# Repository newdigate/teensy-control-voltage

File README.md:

# teensy control voltage analog computer shield 

[![built with kicad](https://img.shields.io/badge/project-v5.1.6-brightgreen.svg?label=kicad&colorA=555555&colorB=8a8fff&logo=
)](https://kicad.org/)

**open source [hardware](hardware) ~~and [software](software)~~ for a [teensy 4.1](https://www.pjrc.com/store/teensy40.html "teensy 4.1 board") eurorack control voltage shield** 

extend a [teensy 4.1](https://www.pjrc.com/store/teensy40.html "teensy 4.1 board") with peripherals to interface with eurorack modular equipment. 

## specifications
* **microcontrollers:** 
  * 600 Mhz ARM cortex m7 ( [teensy 4.1 board](https://www.pjrc.com/store/teensy41.html "teensy 4.1 board") )
* **display:** ST7735 128x128 16bit-color tft display
* **breakouts:** 
  * microSD card socket, 
  * USB host/device, 
  * midi in/out, 
  * 1 x encoders w/switch
* **panel:** 14HP aluminium panel mounted for eurorack case
* **programability**: 
  * write arduino compatible c/c++ firmware & program using arduino/teensyduino
  * arm gnu toolchain [downloads](https://developer.arm.com/tools-and-software/open-source-software/developer-tools/gnu-toolchain/gnu-rm/downloads)
  * teensy [audio library](https://www.pjrc.com/teensy/gui/)

## MIT open source license
* MIT license unless otherwise specified on a per file basis.

## Open source software stack
* All [schematics](hardware/CIRCUITS.md) and boards are created using [Kicad](http://kicad.org/) 
* All mechanical designs are created using [FreeCAD](https://github.com/FreeCAD/FreeCAD)
* Some images have been rendered using [Blender 2.81](https://www.blender.org/)

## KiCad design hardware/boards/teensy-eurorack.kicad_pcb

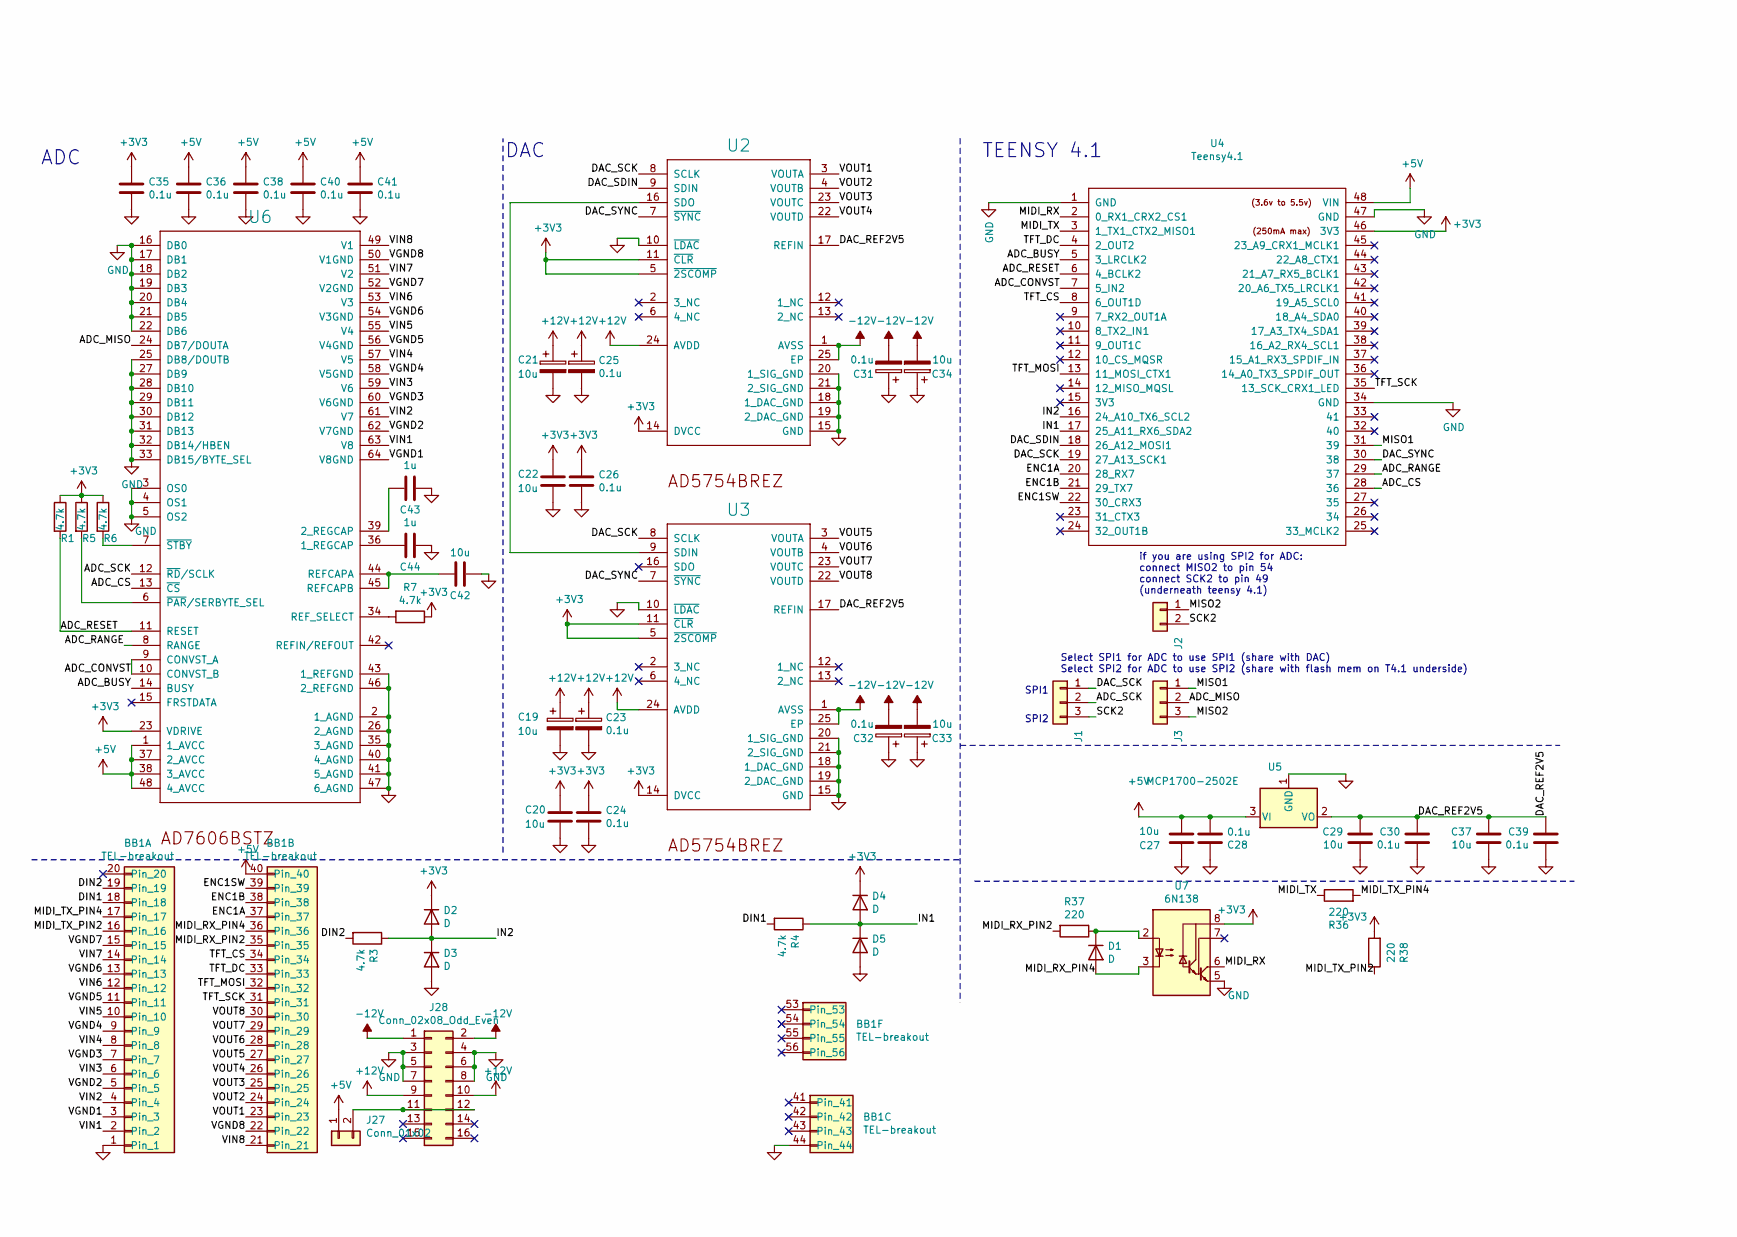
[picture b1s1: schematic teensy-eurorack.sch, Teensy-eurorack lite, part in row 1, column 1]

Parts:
BB1: TEL-breakout; TElite-breakout-board
C19, C21, C33, C34: 10u; CP_Radial_D5.0mm_P2.00mm
C20, C22, C27, C29, C37, C42: 10u; C_0805_2012Metric
C23, C25, C31, C32: 0.1u; CP_Radial_D5.0mm_P2.00mm
C24, C26, C28, C30, C35, C36, C38, C39, C40, C41: 0.1u; C_0805_2012Metric
C43, C44: 1u; C_0805_2012Metric
D1, D2, D3, D4, D5: D; D_0805_2012Metric
J1, J3: Conn_01x03; Pin_Header_Straight_1x03_Pitch2.54mm
J2: Conn_01x02; Pin_Header_Straight_1x02_Pitch2.54mm
J27: Conn_01x02; PinHeader_1x02_P2.54mm_Vertical
J28: Conn_02x08_Odd_Even; PinHeader_2x08_P2.54mm_Vertical
R1, R3, R4, R5, R6, R7: 4.7k; R_0805_2012Metric
R36, R37, R38: 220; R_0805_2012Metric
U2, U3: AD5754BREZ; HTSSOP-24-1EP_4.4x7.8mm_P0.65mm_EP3.2x5mm
U4: Teensy4.1; Teensy41_tht
U5: MCP1700-2502E; SOT-23
U6: AD7606BSTZ; LQFP-64_10x10mm_P0.5mm
U7: 6N138; 6N138S

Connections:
+3V3: C20.1, C22.1, C24.1, C26.1, C35.1, D2.1 (K), D4.1 (K), R1.1, R5.1, R6.1, R7.1, R38.2, U2.5 (~2SCOMP~), U2.11 (~CLR~), U2.14 (DVCC), U3.5 (~2SCOMP~), U3.11 (~CLR~), U3.14 (DVCC), U4.46 (3V3), U6.23 (VDRIVE), U7.8 (VCC)
+5V: BB1.40, C27.2, C28.2, C36.1, C38.1, C40.1, C41.1, J27.1, U4.48 (VIN), U5.3 (VI), U6.1 (1_AVCC), U6.37 (2_AVCC), U6.38 (3_AVCC), U6.48 (4_AVCC)
+12V: C19.1, C21.1, C23.1, C25.1, J28.9, J28.10, U2.24 (AVDD), U3.24 (AVDD)
-12V: C31.2, C32.2, C33.2, C34.2, J28.1, J28.2, U2.1 (AVSS), U2.25 (EP), U3.1 (AVSS), U3.25 (EP)
/ADC_BUSY: U4.5 (3_LRCLK2), U6.14 (BUSY)
/ADC_CONVST: U4.7 (5_IN2), U6.9 (CONVST_A), U6.10 (CONVST_B)
/ADC_CS: U4.28 (36), U6.13 (~CS~)
/ADC_MISO: J3.2, U6.24 (DB7/DOUTA)
/ADC_RANGE: U4.29 (37), U6.8 (RANGE)
/ADC_RESET: R1.2, U4.6 (4_BCLK2), U6.11 (RESET)
/ADC_SCK: J1.2, U6.12 (~RD~/SCLK)
/DAC_REF2V5: C29.1, C30.1, C37.1, C39.1, U2.17 (REFIN), U3.17 (REFIN), U5.2 (VO)
/DAC_SCK: J1.1, U2.8 (SCLK), U3.8 (SCLK), U4.19 (27_A13_SCK1)
/DAC_SDIN: U2.9 (SDIN), U4.18 (26_A12_MOSI1)
/DAC_SYNC: U2.7 (~SYNC~), U3.7 (~SYNC~), U4.30 (38)
/DIN1: BB1.18, R4.2
/DIN2: BB1.19, R3.2
/ENC1A: BB1.37, U4.20 (28_RX7)
/ENC1B: BB1.38, U4.21 (29_TX7)
/ENC1SW: BB1.39, U4.22 (30_CRX3)
/IN1: D4.2 (A), D5.1 (K), R4.1, U4.17 (25_A11_RX6_SDA2)
/IN2: D2.2 (A), D3.1 (K), R3.1, U4.16 (24_A10_TX6_SCL2)
/MIDI_RX: U4.2 (0_RX1_CRX2_CS1), U7.6 (VO2)
/MIDI_RX_PIN2: BB1.35, R37.2
/MIDI_RX_PIN4: BB1.36, D1.2 (A), U7.3 (C2)
/MIDI_TX: R36.1, U4.3 (1_TX1_CTX2_MISO1)
/MIDI_TX_PIN2: BB1.16, R38.1
/MIDI_TX_PIN4: BB1.17, R36.2
/MISO1: J3.1, U4.31 (39)
/MISO2: J2.1, J3.3
/SCK2: J1.3, J2.2
/TFT_CS: BB1.34, U4.8 (6_OUT1D)
/TFT_DC: BB1.33, U4.4 (2_OUT2)
/TFT_MOSI: BB1.32, U4.13 (11_MOSI_CTX1)
/TFT_SCK: BB1.31, U4.35 (13_SCK_CRX1_LED)
/VGND1: BB1.3, U6.64 (V8GND)
/VGND2: BB1.5, U6.62 (V7GND)
/VGND3: BB1.7, U6.60 (V6GND)
/VGND4: BB1.9, U6.58 (V5GND)
/VGND5: BB1.11, U6.56 (V4GND)
/VGND6: BB1.13, U6.54 (V3GND)
/VGND7: BB1.15, U6.52 (V2GND)
/VGND8: BB1.22, U6.50 (V1GND)
/VIN1: BB1.2, U6.63 (V8)
/VIN2: BB1.4, U6.61 (V7)
/VIN3: BB1.6, U6.59 (V6)
/VIN4: BB1.8, U6.57 (V5)
/VIN5: BB1.10, U6.55 (V4)
/VIN6: BB1.12, U6.53 (V3)
/VIN7: BB1.14, U6.51 (V2)
/VIN8: BB1.21, U6.49 (V1)
/VOUT1: BB1.23, U2.3 (VOUTA)
/VOUT2: BB1.24, U2.4 (VOUTB)
/VOUT3: BB1.25, U2.23 (VOUTC)
/VOUT4: BB1.26, U2.22 (VOUTD)
/VOUT5: BB1.27, U3.3 (VOUTA)
/VOUT6: BB1.28, U3.4 (VOUTB)
/VOUT7: BB1.29, U3.23 (VOUTC)
/VOUT8: BB1.30, U3.22 (VOUTD)
GND: BB1.1, BB1.44, C19.2, C20.2, C21.2, C22.2, C23.2, C24.2, C25.2, C26.2, C27.1, C28.1, C29.2, C30.2, C31.1, C32.1, C33.1, C34.1, C35.2, C36.2, C37.2, C38.2, C39.2, C40.2, C41.2, C42.1, C43.1, C44.1, D3.2 (A), D5.2 (A), J28.3, J28.4, J28.5, J28.6, J28.7, J28.8, U2.10 (~LDAC~), U2.15 (GND), U2.18 (1_DAC_GND), U2.19 (2_DAC_GND), U2.20 (1_SIG_GND), U2.21 (2_SIG_GND), U3.10 (~LDAC~), U3.15 (GND), U3.18 (1_DAC_GND), U3.19 (2_DAC_GND), U3.20 (1_SIG_GND), U3.21 (2_SIG_GND), U4.1 (GND), U4.34 (GND), U4.47 (GND), U5.1 (GND), U6.2 (1_AGND), U6.3 (OS0), U6.4 (OS1), U6.5 (OS2), U6.16 (DB0), U6.17 (DB1), U6.18 (DB2), U6.19 (DB3), U6.20 (DB4), U6.21 (DB5), U6.22 (DB6), U6.25 (DB8/DOUTB), U6.26 (2_AGND), U6.27 (DB9), U6.28 (DB10), U6.29 (DB11), U6.30 (DB12), U6.31 (DB13), U6.32 (DB14/HBEN), U6.33 (DB15/BYTE_SEL), U6.35 (3_AGND), U6.40 (4_AGND), U6.41 (5_AGND), U6.43 (1_REFGND), U6.46 (2_REFGND), U6.47 (6_AGND), U7.5 (GND)
unnamed: C42.2, U6.44 (REFCAPA), U6.45 (REFCAPB)
unnamed: C43.2, U6.39 (2_REGCAP)
unnamed: C44.2, U6.36 (1_REGCAP)
unnamed: D1.1 (K), R37.1, U7.2 (C1)
unnamed: J27.2, J28.11, J28.12
unnamed: R5.2, U6.6 (~PAR~/SERBYTE_SEL)
unnamed: R6.2, U6.7 (~STBY~)
unnamed: R7.2, U6.34 (REF_SELECT)
unnamed: U2.16 (SDO), U3.9 (SDIN)

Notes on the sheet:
TEENSY 4.1
ADC
DAC
if you are using SPI2 for ADC: connect MISO2 to pin 54 connect SCK2 to pin 49 (underneath teensy 4.1)
Select SPI1 for ADC to use SPI1 (share with DAC) Select SPI2 for ADC to use SPI2 (share with flash mem on T4.1 underside)
SPI1
SPI2

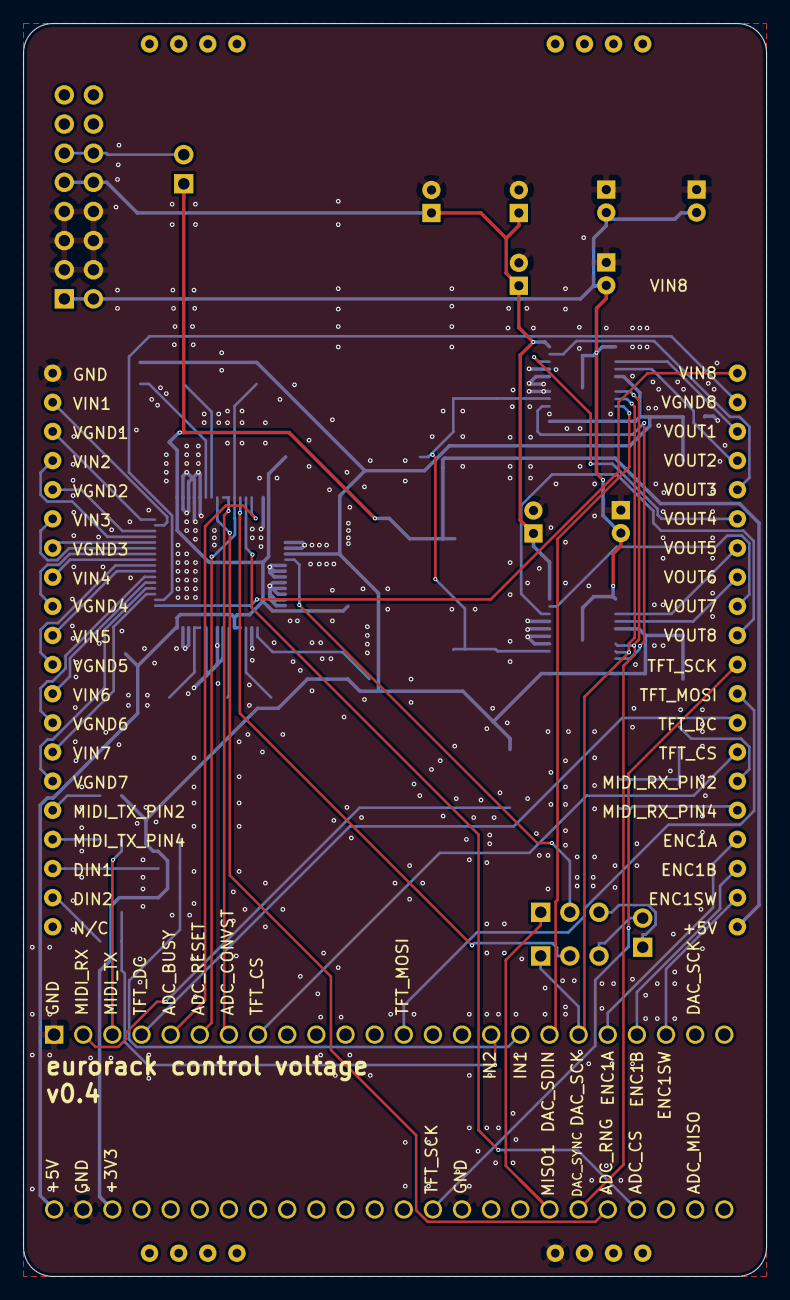
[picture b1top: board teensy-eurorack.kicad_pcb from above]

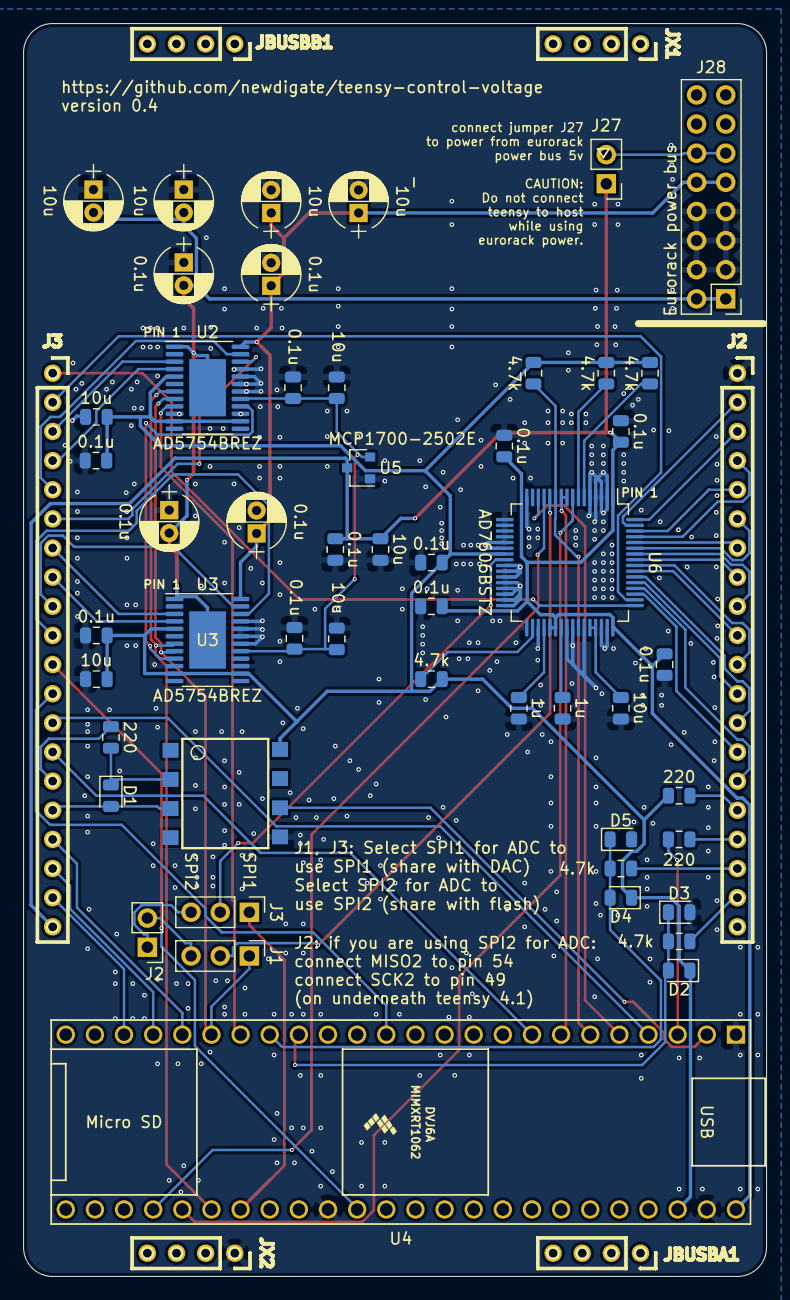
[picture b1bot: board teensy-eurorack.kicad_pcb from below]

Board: 2 copper layers, 64.8 x 109.2 mm, 52 parts (51 on the bottom side), 69 nets.

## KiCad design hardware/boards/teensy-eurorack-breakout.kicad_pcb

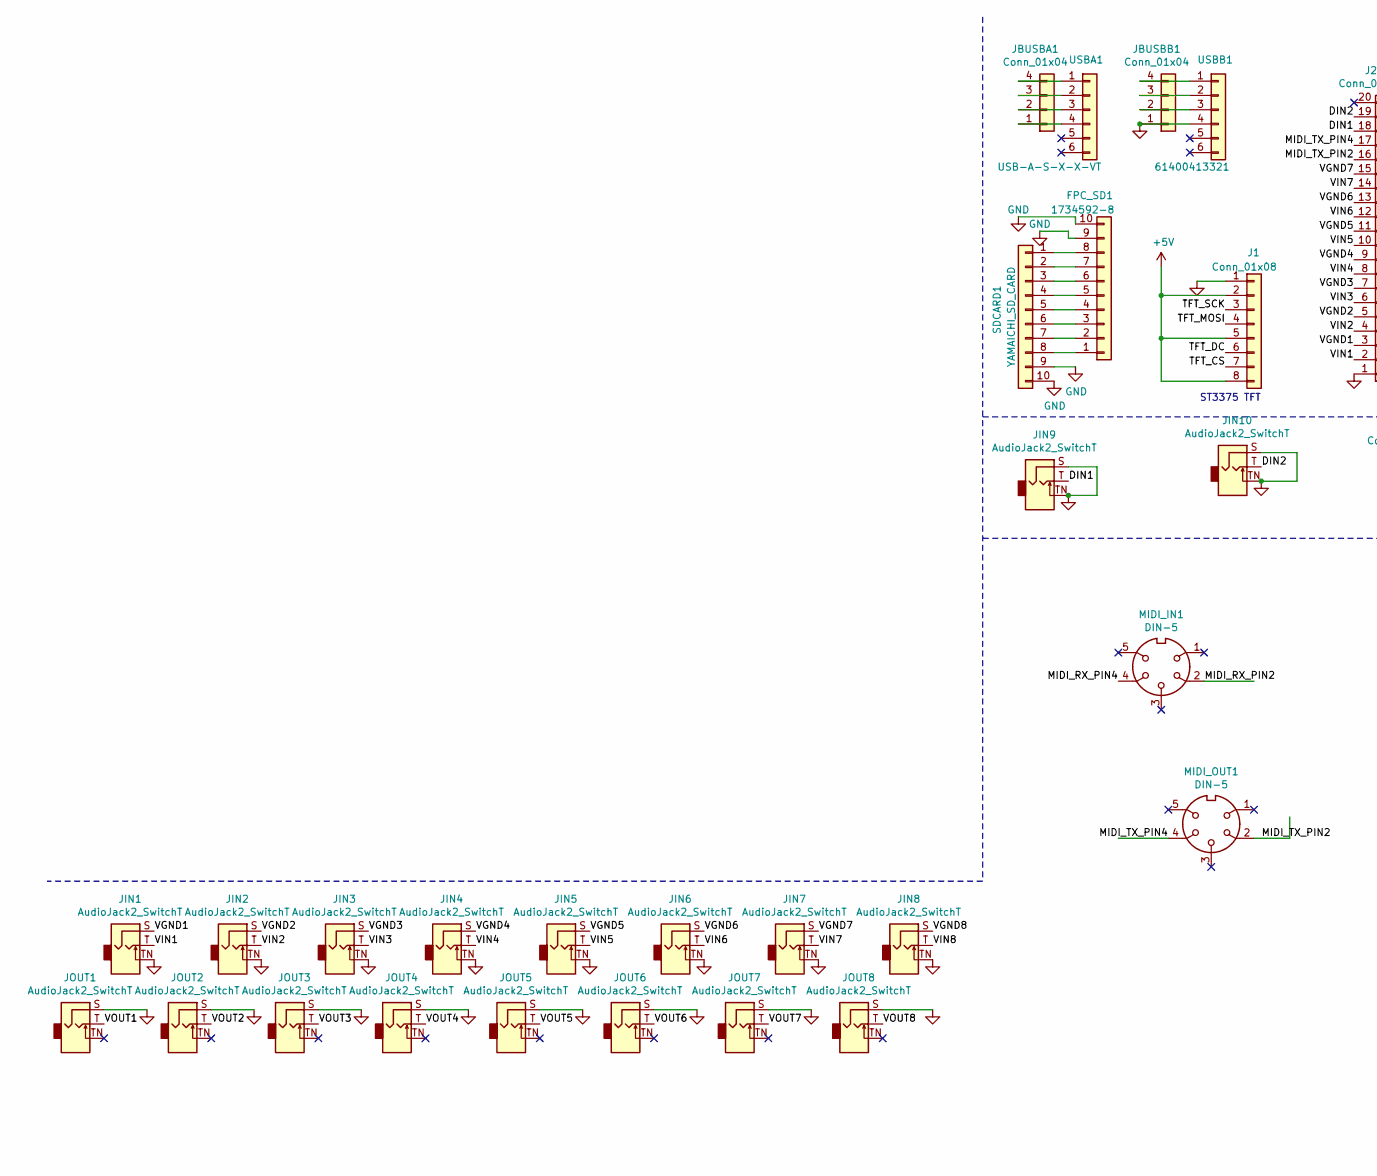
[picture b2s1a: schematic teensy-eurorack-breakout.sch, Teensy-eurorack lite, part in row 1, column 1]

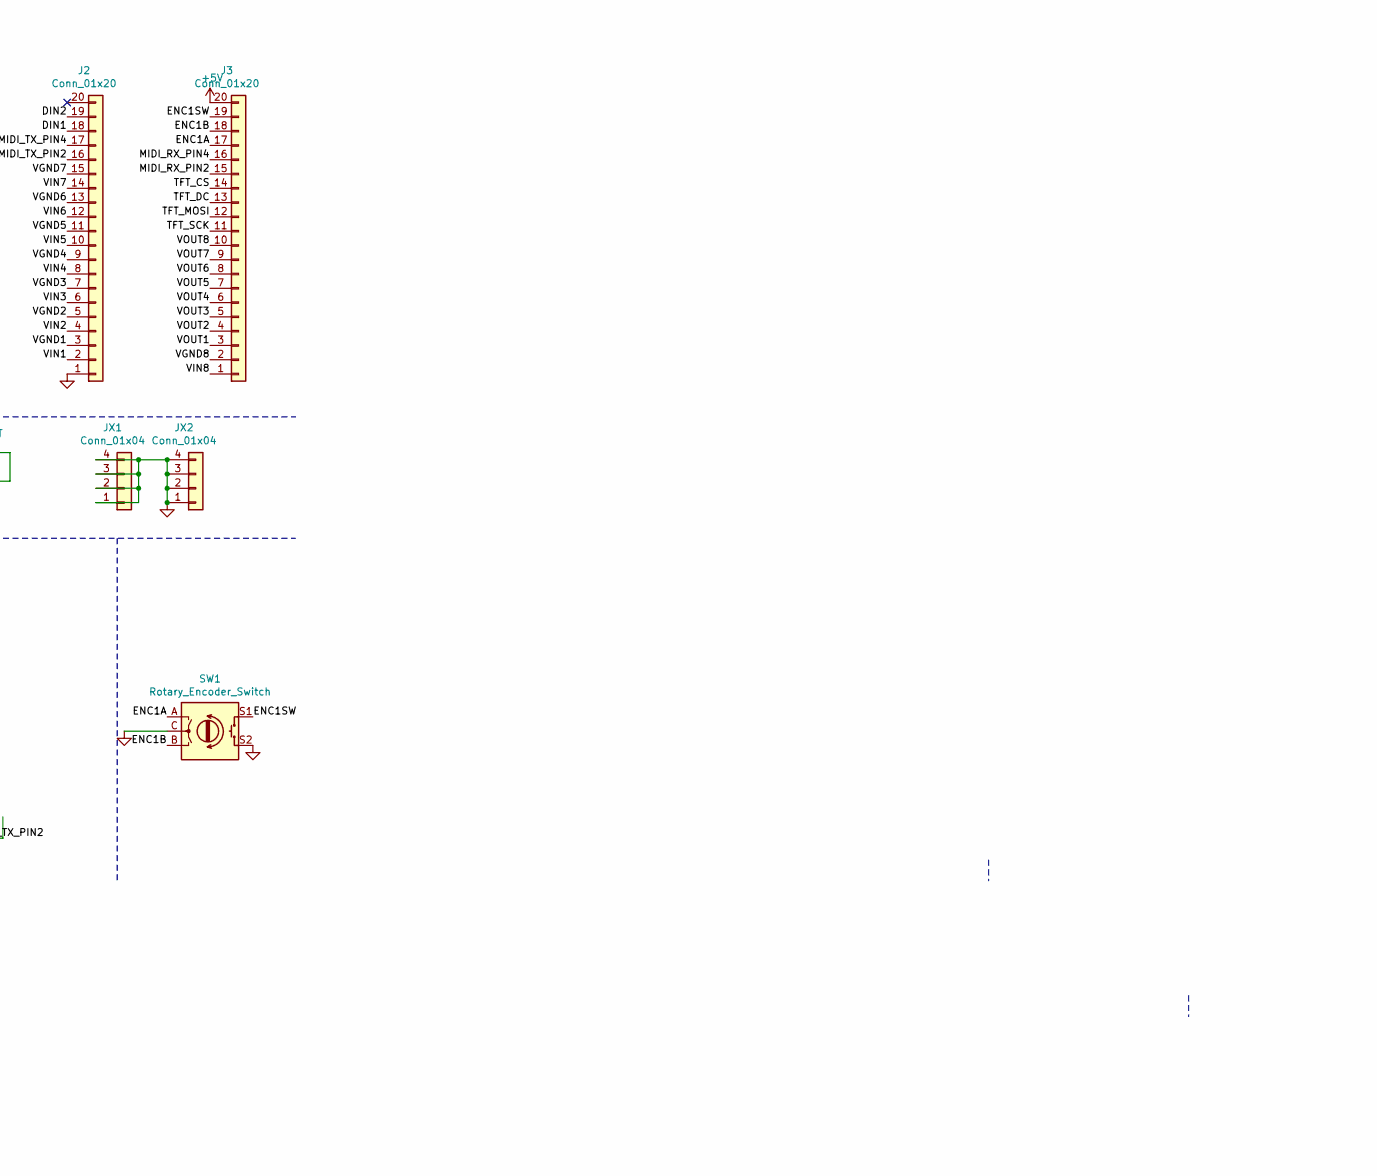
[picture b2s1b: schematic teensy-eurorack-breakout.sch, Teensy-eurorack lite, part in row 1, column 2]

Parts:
FPC_SD1: 1734592-8; HFW8R-1STE1LF
J1: Conn_01x08; ST7735
J2, J3: Conn_01x20; PinSocket_1x20_P2.54mm_Vertical
JBUSBA1: Conn_01x04; PinSocket_1x04_P2.54mm_Vertical
JBUSBB1: Conn_01x04; PinSocket_1x04_P2.54mm_Vertical
JIN1, JIN2, JIN3, JIN4, JIN5, JIN6, JIN7, JIN8, JIN9, JIN10: AudioJack2_SwitchT; WQP-PJ301M-12_JACK
JOUT1, JOUT2, JOUT3, JOUT4, JOUT5, JOUT6, JOUT7, JOUT8: AudioJack2_SwitchT; WQP-PJ301M-12_JACK
JX1, JX2: Conn_01x04; PinSocket_1x04_P2.54mm_Vertical
MIDI_IN1: DIN-5; OG-MIDI_SD-50BV
MIDI_OUT1: DIN-5; OG-MIDI_SD-50BV
SDCARD1: YAMAICHI_SD_CARD; YAMAICHI_MICROSD_VERTICAL
SW1: Rotary_Encoder_Switch; RotaryEncoder_Alps_EC12E-Switch_Vertical_H20mm_CircularMoun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
USBA1: USB-A-S-X-X-VT
USBB1: 61400413321; WURTH_ELECTRONICS_61400413321_0

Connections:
+5V: J1.2, J1.5, J1.8, J3.20
/DIN1: J2.18, JIN9.T
/DIN2: J2.19, JIN10.T
/ENC1A: J3.17, SW1.A
/ENC1B: J3.18, SW1.B
/ENC1SW: J3.19, SW1.S1
/MIDI_RX_PIN2: J3.15, MIDI_IN1.2
/MIDI_RX_PIN4: J3.16, MIDI_IN1.4
/MIDI_TX_PIN2: J2.16, MIDI_OUT1.2
/MIDI_TX_PIN4: J2.17, MIDI_OUT1.4
/TFT_CS: J1.7, J3.14
/TFT_DC: J1.6, J3.13
/TFT_MOSI: J1.4, J3.12
/TFT_SCK: J1.3, J3.11
/VGND1: J2.3, JIN1.S
/VGND2: J2.5, JIN2.S
/VGND3: J2.7, JIN3.S
/VGND4: J2.9, JIN4.S
/VGND5: J2.11, JIN5.S
/VGND6: J2.13, JIN6.S
/VGND7: J2.15, JIN7.S
/VGND8: J3.2, JIN8.S
/VIN1: J2.2, JIN1.T
/VIN2: J2.4, JIN2.T
/VIN3: J2.6, JIN3.T
/VIN4: J2.8, JIN4.T
/VIN5: J2.10, JIN5.T
/VIN6: J2.12, JIN6.T
/VIN7: J2.14, JIN7.T
/VIN8: J3.1, JIN8.T
/VOUT1: J3.3, JOUT1.T
/VOUT2: J3.4, JOUT2.T
/VOUT3: J3.5, JOUT3.T
/VOUT4: J3.6, JOUT4.T
/VOUT5: J3.7, JOUT5.T
/VOUT6: J3.8, JOUT6.T
/VOUT7: J3.9, JOUT7.T
/VOUT8: J3.10, JOUT8.T
GND: FPC_SD1.9, FPC_SD1.10, J1.1, J2.1, JBUSBB1.1, JIN1.TN, JIN2.TN, JIN3.TN, JIN4.TN, JIN5.TN, JIN6.TN, JIN7.TN, JIN8.TN, JIN9.S, JIN9.TN, JIN10.S, JIN10.TN, JOUT1.S, JOUT2.S, JOUT3.S, JOUT4.S, JOUT5.S, JOUT6.S, JOUT7.S, JOUT8.S, JX1.1, JX1.2, JX1.3, JX1.4, JX2.1, JX2.2, JX2.3, JX2.4, SDCARD1.9, SDCARD1.10, SW1.C, SW1.S2, USBB1.4
unnamed: FPC_SD1.1, SDCARD1.8
unnamed: FPC_SD1.2, SDCARD1.7
unnamed: FPC_SD1.3, SDCARD1.6
unnamed: FPC_SD1.4, SDCARD1.5
unnamed: FPC_SD1.5, SDCARD1.4
unnamed: FPC_SD1.6, SDCARD1.3
unnamed: FPC_SD1.7, SDCARD1.2
unnamed: FPC_SD1.8, SDCARD1.1
unnamed: JBUSBA1.1, USBA1.4
unnamed: JBUSBA1.2, USBA1.3
unnamed: JBUSBA1.3, USBA1.2
unnamed: JBUSBA1.4, USBA1.1
unnamed: JBUSBB1.2, USBB1.3
unnamed: JBUSBB1.3, USBB1.2
unnamed: JBUSBB1.4, USBB1.1

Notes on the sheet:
ST3375 TFT

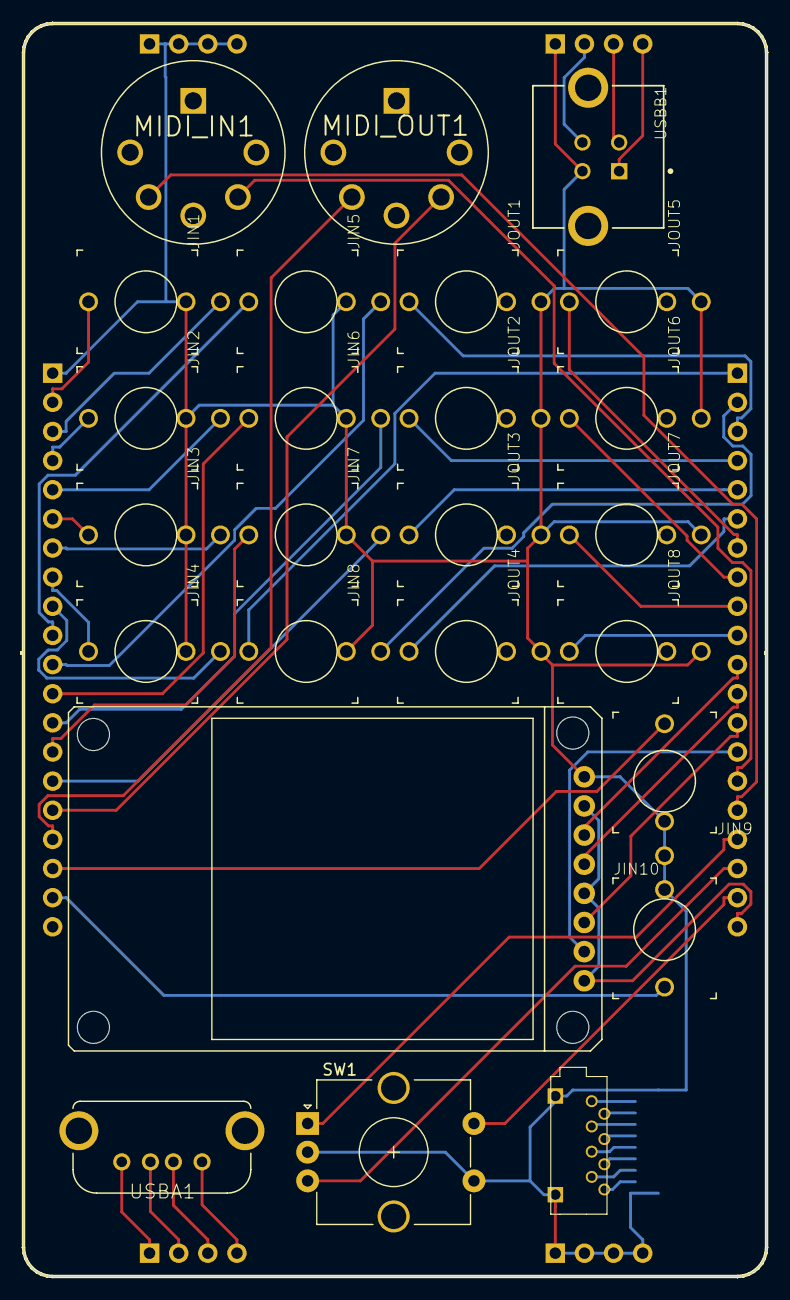
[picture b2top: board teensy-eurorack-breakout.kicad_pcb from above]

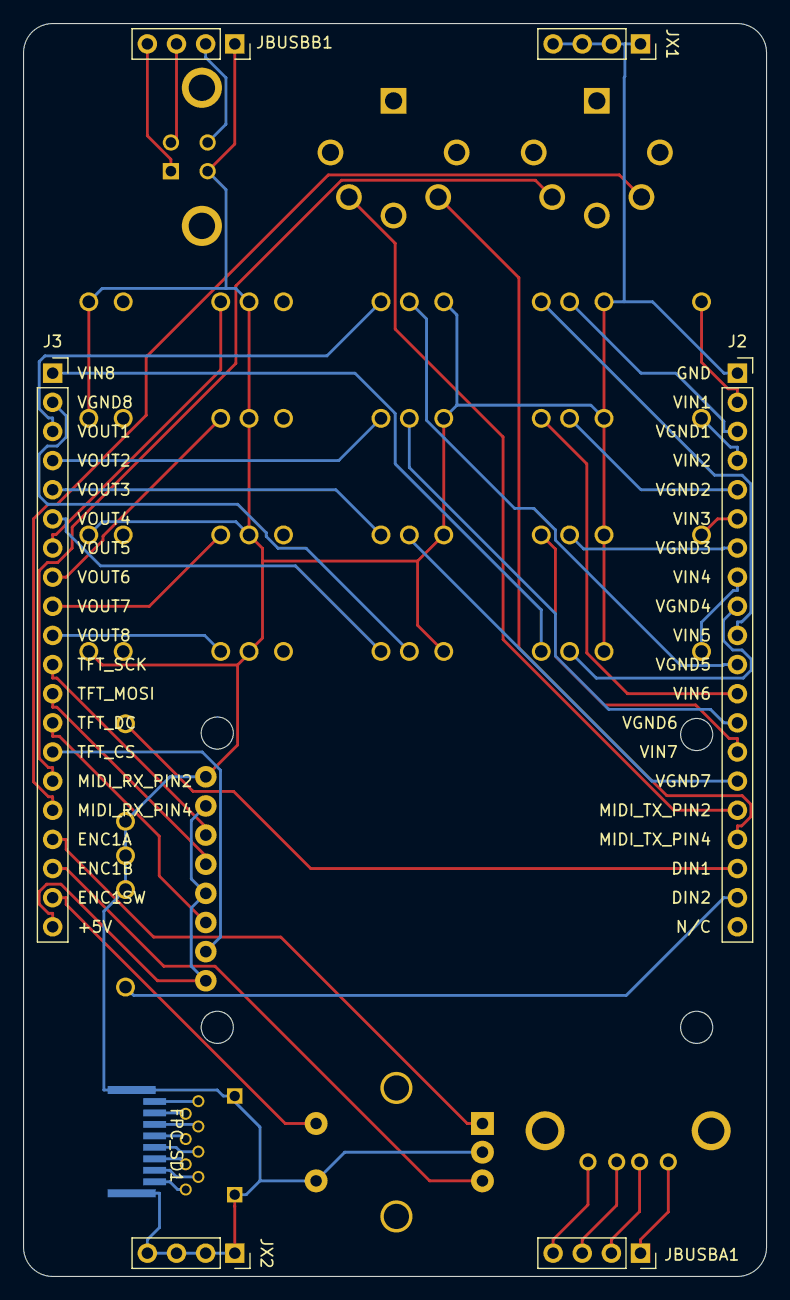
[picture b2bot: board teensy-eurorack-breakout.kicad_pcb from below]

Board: 2 copper layers, 64.8 x 109.2 mm, 32 parts (7 on the bottom side), 54 nets.

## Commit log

2020-09-20 docs...
2020-09-23 schematic: fix ad7606 pin 8 (range select) from tied to gnd via res, to tied to 3v3 via resistor
2020-09-23 schematic: hookup ADC_RESET via pullup and ENC1A, ENC1B, ENC1SW
2020-09-23 schematic: move IN1 IN2 from pins 38,39 to 24,25; moved some text / reference designators
2020-09-23 image: mainboard circuit updated
2020-09-23 pull changes from schematic, reroute as double layer board
2020-09-23 add gerbers for front-panel
2020-10-04 add interactive BOM for mainboard and breakout
2020-10-13 symbol: corrected pins on teensy 4.1
2020-10-13 updated schematic with jumpers to configure ADC to use either SPI1 or SPI2
2020-10-13 correct footprint to pin headers for jumpers
2020-10-14 rerouted pcb
2020-10-14 3d model
2020-10-14 updated to reference step files
2020-10-14 update gerbers
2020-10-14 silkscreen corrections
2020-10-26 MISO corrected from pin 41 to pin 39, teensy symbol corrections
2020-10-26 don't need cache for symbols to be committed
2020-10-26 corrections applied to pcb, miso to pin 39
2020-10-26 silkscreen corrections and updated to version 0.4
2020-10-26 Revert "don't need cache for symbols to be committed"
    This reverts commit ca6b8780522b1148d48669fbbe2aa83ee91aeef5.
2020-11-28 schematic: change dac bypass to polarized cap and change polarity
2020-11-28 pcb: correction to polarity of bypass caps
2021-11-08 Update README.md
    https://forum.kicad.info/t/warning-avoid-all-links-to-kicad-pcb-org-use-kicad-org/31521
